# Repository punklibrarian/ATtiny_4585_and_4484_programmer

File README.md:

ATtiny 44/84 and 45/85 Programmer
=================================
Copyright 2011 Design Tech Industries (DTI)

DTI email: <jameskun89@rocketmail.com>

The **ATtiny 44/84 and 45/85 Programmer** is the continuation of a project I started one Saturday afternoon, that being the ATtiny Programmer Shield
(https://github.com/punklibrarian/ATtiny_45_and_85_programmer_shield). It uses an ATMega328 running the Arduino boot loader and the ArduinoISP sketch to 
program ATtiny 44/84 and 45/85 micro controllers. It uses what I learnt from reading the tutorials at High-Low Tech on programming ATtiny's using an Arduino
(http://hlt.media.mit.edu/?p=1229 http://hlt.media.mit.edu/?p=1695).

Features:

 * Activity LEDs
 * ATtiny 45/85 Pin 0 LED (for Blink sketch test) 
 * ATtiny 44/84 Pin 6 LED (for Blink sketch test)
 * ATMega328 Pin 13 LED (for Blink sketch test)
 * A 10uF capacitor between RST and GND to stop Arduino auto-resetting. 
 * Open Source; OSHW compliant
 * Design files freely available

In this repository you will find the gerber files for BatchPCB (http://batchpcb.com), along with project (.pro), board (.brd) 
and schematic (.sch) files for this shield in the 'EAGLE and 'KiCad' folders. 

INSTALLATION
------------
**EAGLE**
The design is saved as an EAGLE project. EAGLE PCB design software is available from www.cadsoftusa.com 
free for non-commercial use and can be installed on Windows and Mac, with Linux support through WINE. 
To use this project download it and place the directory containing these files into the "eagle" directory 
on your computer. Then open EAGLE and navigate to Projects -> eagle -> ATtiny_4585_and_4484_programmer.

**KiCad**
KiCad EDA Suite is an Open Source alternative to EAGLE. It is available on Windows and Linux and can be installed 
on Mac. It is available from http://kicad.sourceforge.net and works in a similar way to EAGLE. You will find project 
files for KiCad in the aptly named folder in this repository. To use this project download it and place the directory 
containing these files into a folder of your choice. Then open KiCad and navigate to File -> Open -> 
'FOLDER_OF_YOUR_CHOICE' -> ATtiny_4585_and_4484_programmer.pro

HOW TO USE
----------
Follow instructions outlined in this section at the ATtiny 45 and 85 Programmer Shield (https://github.com/punklibrarian/ATtiny_45_and_85_programmer_shield).

DISTRIBUTION
------------
The specific terms of distribution of this project are governed by the license referenced below.

LICENSE
-------
> This work is licensed under the Creative Commons Attribution-ShareAlike License.  
> 
> To view a copy of this license, visit:
> 
>   http://creativecommons.org/licenses/by-sa/3.0/  
>   http://creativecommons.org/licenses/by-sa/3.0/legalcode
> 
> or send a letter to
> 
>   Creative Commons  
>   171 Second Street, Suite 300  
>   San Francisco  
>   California, 94105  
>   USA

The "license" folder within this repository also contains copies of the
license(s) referenced above.

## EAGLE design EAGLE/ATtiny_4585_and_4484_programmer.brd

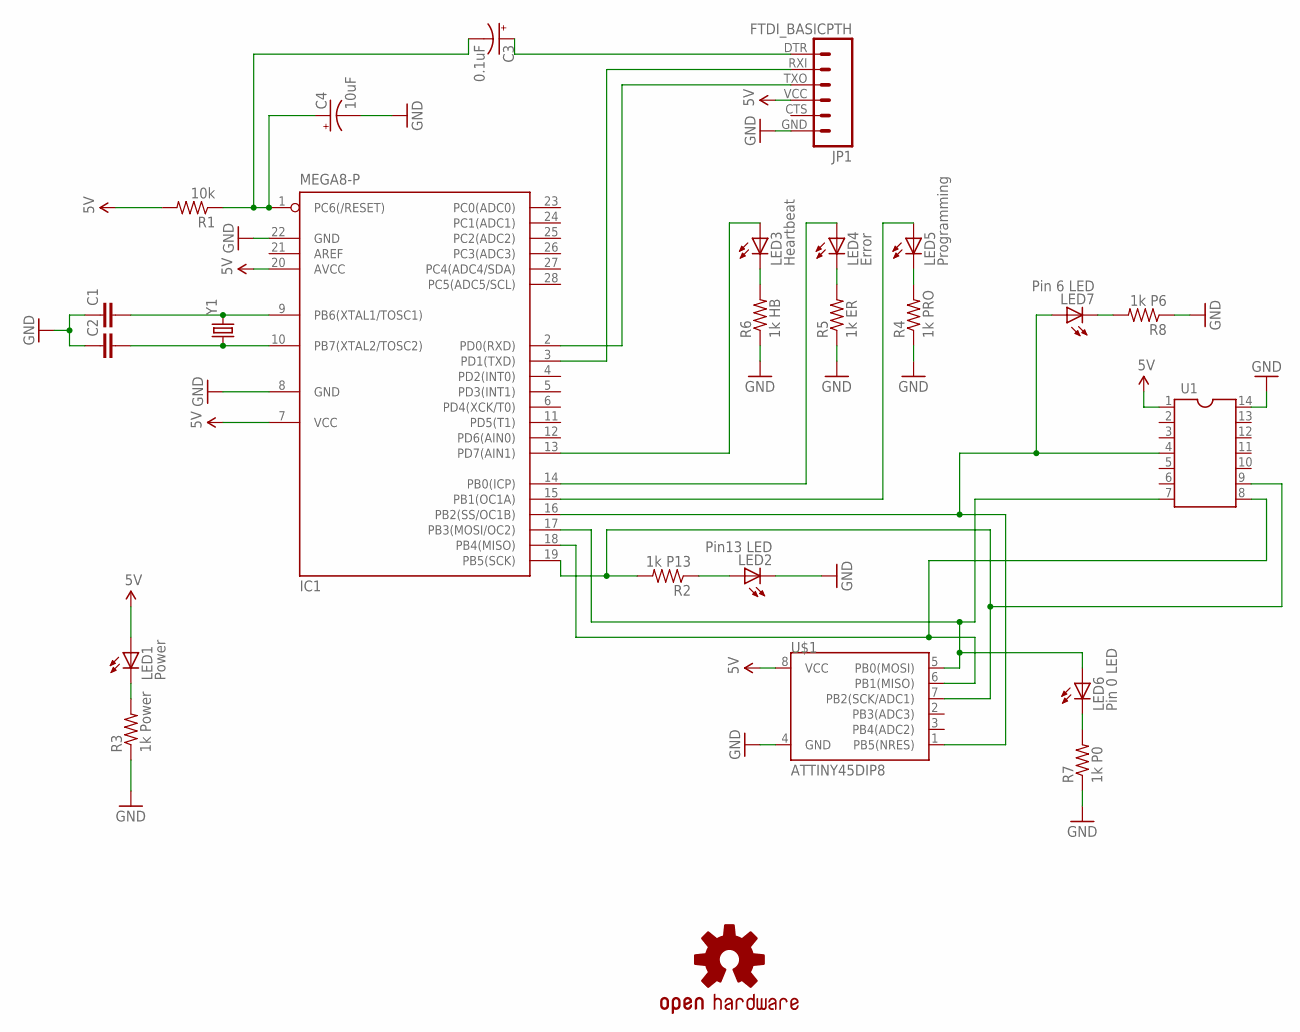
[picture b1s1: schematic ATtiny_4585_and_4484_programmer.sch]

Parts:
C1, C2: CAPPTH; CAP-PTH-SMALL
C3: 0.1uF; CPOL-RADIAL-10UF-25V
C4: 10uF; CPOL-RADIAL-10UF-25V
IC1: MEGA8-P; DIL28-3
JP1: FTDI_BASICPTH; FTDI_BASIC
LED1: Power; LED5MM
LED2: Pin13 LED; LED5MM
LED3: Heartbeat; LED5MM
LED4: Error; LED5MM
LED5: Programming; LED5MM
LED6: Pin 0 LED; LED5MM
LED7: Pin 6 LED; LED5MM
R1: 10k; AXIAL-0.4
R2: 1k P13; AXIAL-0.4
R3: 1k Power; AXIAL-0.4
R4: 1k PRO; AXIAL-0.4
R5: 1k ER; AXIAL-0.4
R6: 1k HB; AXIAL-0.4
R7: 1k P0; AXIAL-0.4
R8: 1k P6; AXIAL-0.4
U1: DIL14
U$1: ATTINY45DIP8; DIP08
U$9: OSHW-LOGOM; OSHW-LOGO-M
Y1: CRYSTALHC49US; HC49US

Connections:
5V: IC1.7 (VCC), IC1.20 (AVCC), JP1.VCC (4), LED1.A, R1.P$2 (2), U1.1, U$1.8 (VCC)
GND: C1.1, C2.1, C4.2 (-), IC1.8 (GND), IC1.22 (GND), JP1.GND (6), LED2.K (C), R3.P$1 (1), R4.P$1 (1), R5.P$1 (1), R6.P$1 (1), R7.P$1 (1), R8.P$1 (1), U1.14, U$1.4 (GND)
unnamed: C1.2, IC1.9 (PB6(XTAL1/TOSC1)), Y1.2
unnamed: C2.2, IC1.10 (PB7(XTAL2/TOSC2)), Y1.1
unnamed: C3.1 (+), JP1.DTR (1)
unnamed: IC1.16 (PB2(SS/OC1B)), LED7.A, U1.4, U$1.1 (PB5(NRES))
unnamed: IC1.3 (PD1(TXD)), JP1.RXI (2)
unnamed: IC1.2 (PD0(RXD)), JP1.TXO (3)
unnamed: LED1.K (C), R3.P$2 (2)
unnamed: IC1.19 (PB5(SCK)), R2.P$2 (2), U1.9, U$1.7 (PB2(SCK/ADC1))
unnamed: LED2.A, R2.P$1 (1)
unnamed: IC1.17 (PB3(MOSI/OC2)), LED6.A, U1.7, U$1.5 (PB0(MOSI))
unnamed: IC1.18 (PB4(MISO)), U1.8, U$1.6 (PB1(MISO))
unnamed: IC1.14 (PB0(ICP)), LED4.A
unnamed: IC1.13 (PD7(AIN1)), LED3.A
unnamed: LED3.K (C), R6.P$2 (2)
unnamed: LED4.K (C), R5.P$2 (2)
unnamed: LED5.K (C), R4.P$2 (2)
unnamed: IC1.15 (PB1(OC1A)), LED5.A
unnamed: C3.2 (-), C4.1 (+), IC1.1 (PC6(/RESET)), R1.P$1 (1)
unnamed: LED6.K (C), R7.P$2 (2)
unnamed: LED7.K (C), R8.P$2 (2)

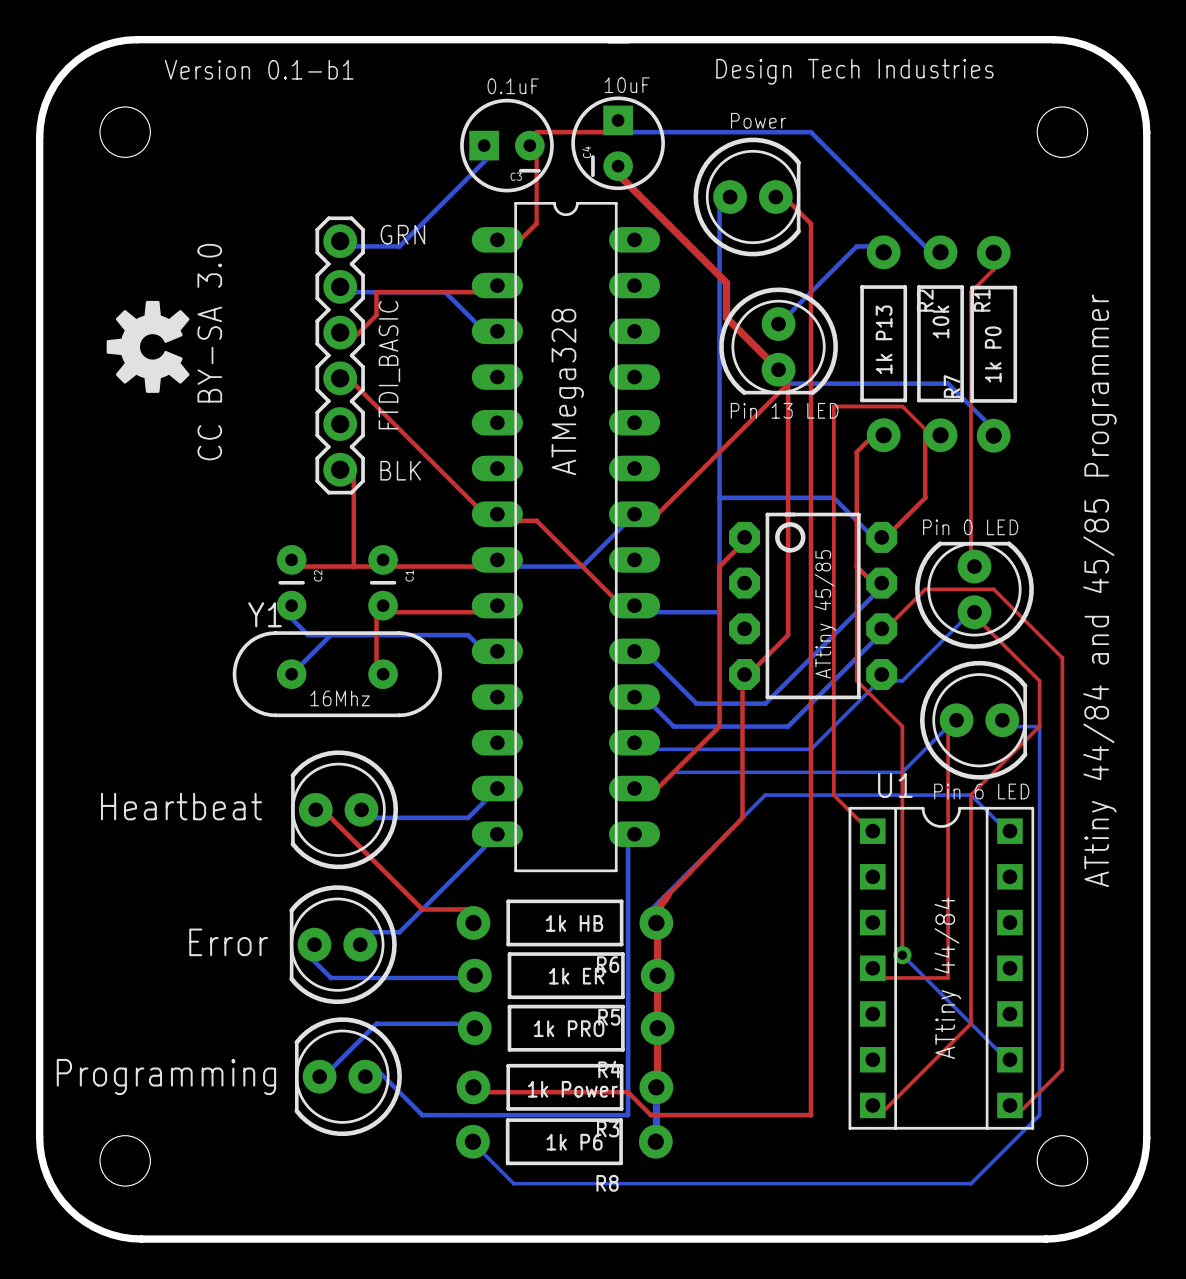
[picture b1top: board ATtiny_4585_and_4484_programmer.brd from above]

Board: 2 copper layers, 61.5 x 66.6 mm, 25 parts (0 on the bottom side), 22 nets.

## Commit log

2011-12-03 Initial commit of files.
2011-12-13 Upgraded to EAGLE 6 and reserved files in new XML format.

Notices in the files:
EAGLE/ATtiny_4585_and_4484_programmer.brd:
CC BY-SA 3.0
